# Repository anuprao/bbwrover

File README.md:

# bbwrover

An 'Easy and Quick' prototype board for the ESP32 Wrover Module with two UARTS.

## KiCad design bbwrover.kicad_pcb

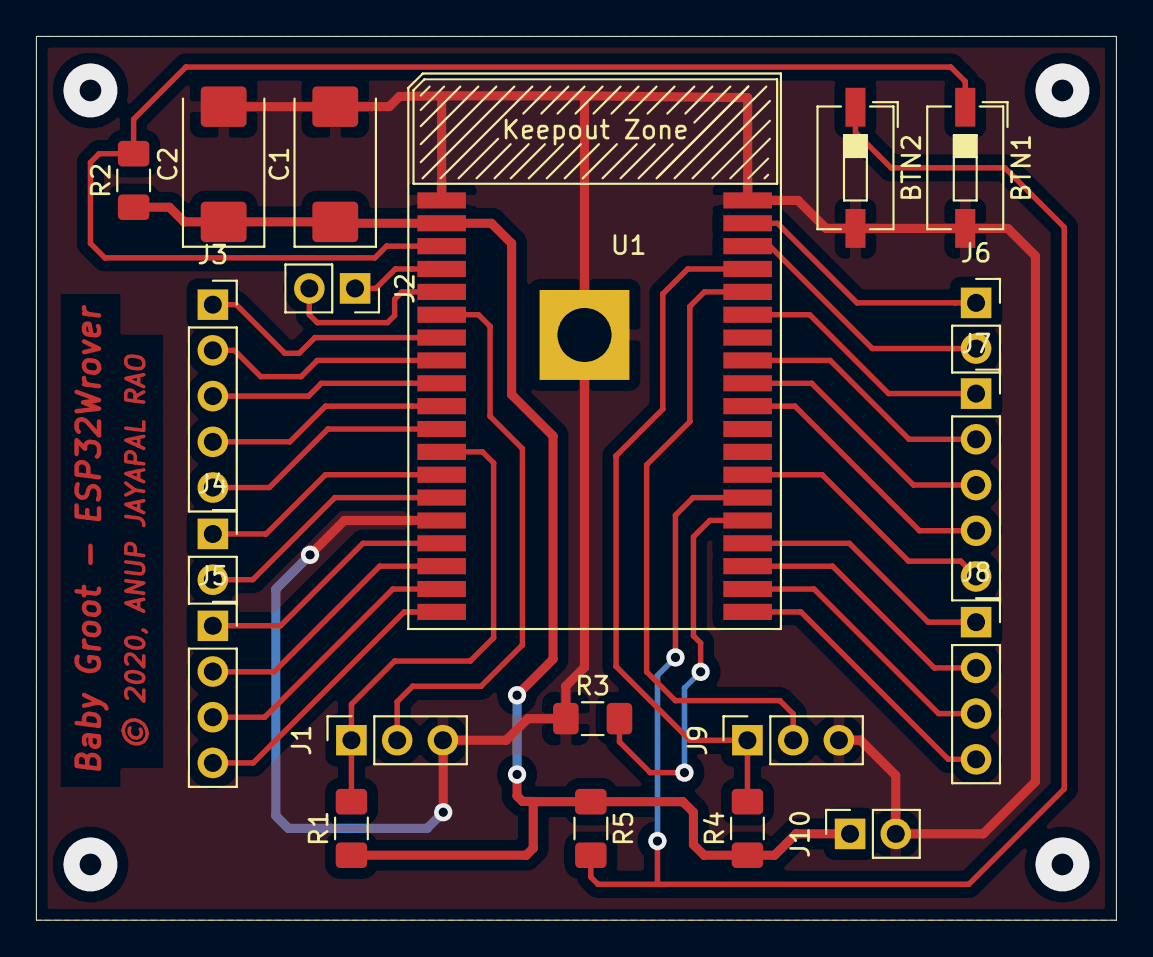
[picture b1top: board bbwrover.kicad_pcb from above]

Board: 2 copper layers, 60.0 x 49.1 mm, 20 parts (0 on the bottom side), 33 nets.

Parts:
BTN1: BTN_EN; SW_DIP_SPSTx01_Slide_6.7x4.1mm_W6.73mm_P2.54mm_LowProfile_J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
BTN2: BTN_FLASH; SW_DIP_SPSTx01_Slide_6.7x4.1mm_W6.73mm_P2.54mm_LowProfile_J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
C1: 100uf; CP_EIA-7343-15_Kemet-W_Pad2.25x2.55mm_HandSolder
C2: 200uf; CP_EIA-7343-15_Kemet-W_Pad2.25x2.55mm_HandSolder
J1: UART2; PinSocket_1x03_P2.54mm_Vertical
J2, J4, J6: Conn; PinSocket_1x02_P2.54mm_Vertical
J3, J7: Conn; PinSocket_1x05_P2.54mm_Vertical
J5, J8: Conn; PinSocket_1x04_P2.54mm_Vertical
J9: UART1; PinSocket_1x03_P2.54mm_Vertical
J10: Power Conn.; PinSocket_1x02_P2.54mm_Vertical
R1, R2, R3, R4, R5: 10K; R_1206_3216Metric_Pad1.42x1.75mm_HandSolder
U1: esp32_wrover; ESP32_Wrover

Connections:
GND: BTN1.2, BTN2.2, C1.2, C2.2, J1.3, J9.3, J10.2, R3.1, U1.1, U1.15, U1.38, U1.39
unnamed: BTN1.1, R2.2, U1.3
unnamed: BTN2.1, R5.2, U1.25
unnamed: J1.1, R1.2, U1.12
unnamed: J1.2, U1.6
unnamed: J2.1, U1.4
unnamed: J2.2, U1.5
unnamed: J3.1, U1.7
unnamed: J3.2, U1.8
unnamed: J3.3, U1.9
unnamed: J3.4, U1.10
unnamed: J3.5, U1.11
unnamed: J4.1, U1.13
unnamed: J4.2, U1.14
unnamed: J5.1, U1.16
unnamed: J5.2, U1.17
unnamed: J5.3, U1.18
unnamed: J5.4, U1.19
unnamed: J6.1, U1.37
unnamed: J6.2, U1.36
unnamed: J7.1, U1.33
unnamed: J7.2, U1.31
unnamed: J7.3, U1.30
unnamed: J7.4, U1.29
unnamed: J7.5, U1.26
unnamed: J8.1, U1.23
unnamed: J8.2, U1.22
unnamed: J8.3, U1.21
unnamed: J8.4, U1.20
unnamed: J9.1, R4.2, U1.35
unnamed: J9.2, U1.34
unnamed: R3.2, U1.24
VCC: C1.1, C2.1, J10.1, R1.1, R2.1, R4.1, R5.1, U1.2

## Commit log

2020-02-01 Update to readme
2020-02-01 Added filled zone for the PCB
2020-02-01 Added sodlermask
2020-02-01 Added PDF version of schematic

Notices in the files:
bbwrover.kicad_pcb:
© 2020, ANUP JAYAPAL RAO
